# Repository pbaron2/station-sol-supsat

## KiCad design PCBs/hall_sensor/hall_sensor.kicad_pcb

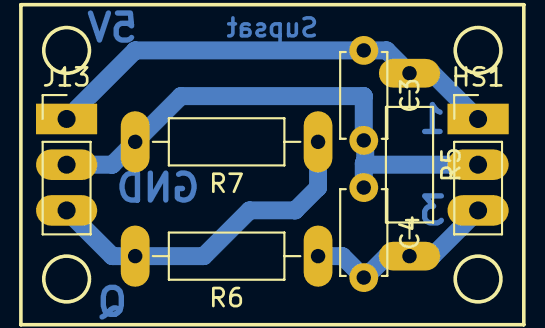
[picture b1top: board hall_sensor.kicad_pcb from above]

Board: 2 copper layers, 7 parts (0 on the bottom side), 4 nets.

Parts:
C3, C4: C; C_Disc_D4.7mm_W2.5mm_P5.00mm
HS1: HALL_SENSOR; Pin_Header_Straight_1x03_Pitch2.54mm
J13: Conn_01x03; Pin_Header_Straight_1x03_Pitch2.54mm
R5, R6, R7: R; R_Axial_DIN0207_L6.3mm_D2.5mm_P10.16mm_Horizontal

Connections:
+5V: C3.1, HS1.1, J13.1, R5.1
GNDPWR: C3.2, C4.1, HS1.2, J13.2, R7.2
unnamed: C4.2, HS1.3, R5.2, R6.1
unnamed: J13.3, R6.2, R7.1

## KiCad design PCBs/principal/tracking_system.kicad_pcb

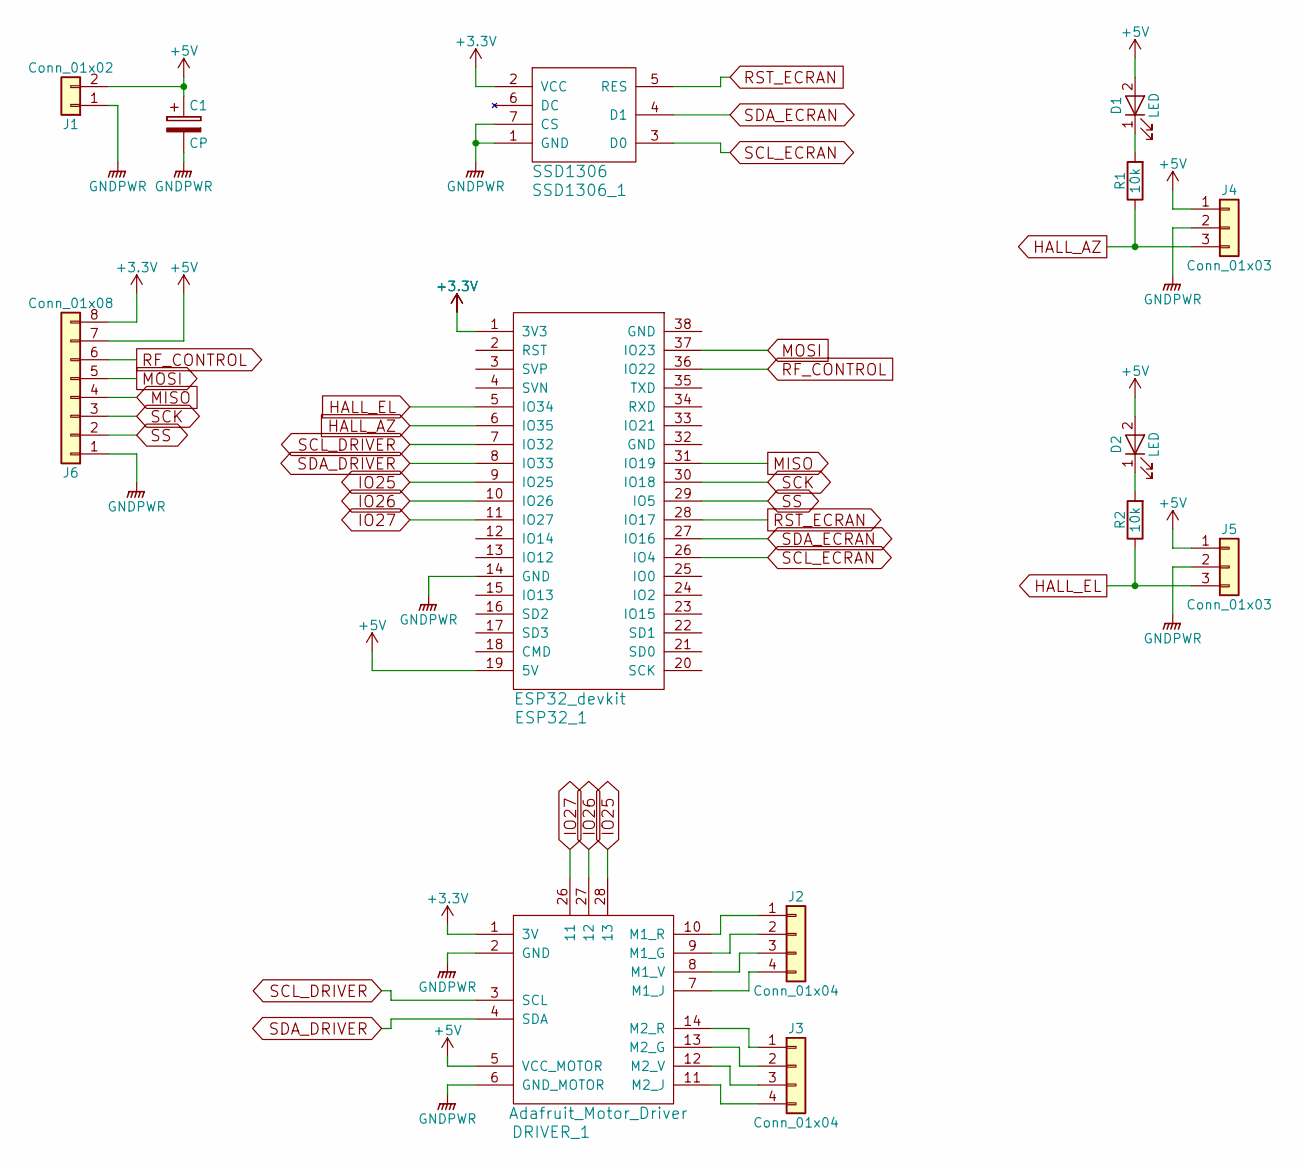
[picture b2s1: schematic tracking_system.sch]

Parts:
C1: CP; CP_Radial_D8.0mm_P2.50mm
D1, D2: LED; LED_D3.0mm
DRIVER_1: Adafruit_Motor_Driver
ESP32_1: ESP32_devkit
J1: Conn_01x02; Pin_Header_Straight_1x02_Pitch2.54mm
J2, J3: Conn_01x04; Pin_Header_Straight_1x04_Pitch2.54mm
J4, J5: Conn_01x03; Pin_Header_Straight_1x03_Pitch2.54mm
J6: Conn_01x08; Pin_Header_Straight_1x08_Pitch2.54mm
R1, R2: 10k; R_Axial_DIN0207_L6.3mm_D2.5mm_P10.16mm_Horizontal
SSD1306_1: SSD1306

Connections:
+3V3: DRIVER_1.1 (3V), ESP32_1.1 (3V3), J6.8, SSD1306_1.2 (VCC)
+5V: C1.1, D1.2 (A), D2.2 (A), DRIVER_1.5 (VCC_MOTOR), ESP32_1.19 (5V), J1.2, J4.1, J5.1, J6.7
GNDPWR: C1.2, DRIVER_1.2 (GND), DRIVER_1.6 (GND_MOTOR), ESP32_1.14 (GND), J1.1, J4.2, J5.2, J6.1, SSD1306_1.1 (GND), SSD1306_1.7 (CS)
HALL_AZ: ESP32_1.6 (IO35), J4.3, R1.1
HALL_EL: ESP32_1.5 (IO34), J5.3, R2.1
IO25: DRIVER_1.28 (13), ESP32_1.9 (IO25)
IO26: DRIVER_1.27 (12), ESP32_1.10 (IO26)
IO27: DRIVER_1.26 (11), ESP32_1.11 (IO27)
MISO: ESP32_1.31 (IO19), J6.4
MOSI: ESP32_1.37 (IO23), J6.5
unnamed: D1.1 (K), R1.2
unnamed: D2.1 (K), R2.2
unnamed: DRIVER_1.7 (M1_J), J2.4
unnamed: DRIVER_1.8 (M1_V), J2.3
unnamed: DRIVER_1.9 (M1_G), J2.2
unnamed: DRIVER_1.10 (M1_R), J2.1
unnamed: DRIVER_1.11 (M2_J), J3.4
unnamed: DRIVER_1.12 (M2_V), J3.3
unnamed: DRIVER_1.13 (M2_G), J3.2
unnamed: DRIVER_1.14 (M2_R), J3.1
RF_CONTROL: ESP32_1.36 (IO22), J6.6
RST_ECRAN: ESP32_1.28 (IO17), SSD1306_1.5 (RES)
SCK: ESP32_1.30 (IO18), J6.3
SCL_DRIVER: DRIVER_1.3 (SCL), ESP32_1.7 (IO32)
SCL_ECRAN: ESP32_1.26 (IO4), SSD1306_1.3 (D0)
SDA_DRIVER: DRIVER_1.4 (SDA), ESP32_1.8 (IO33)
SDA_ECRAN: ESP32_1.27 (IO16), SSD1306_1.4 (D1)
SS: ESP32_1.29 (IO5), J6.2

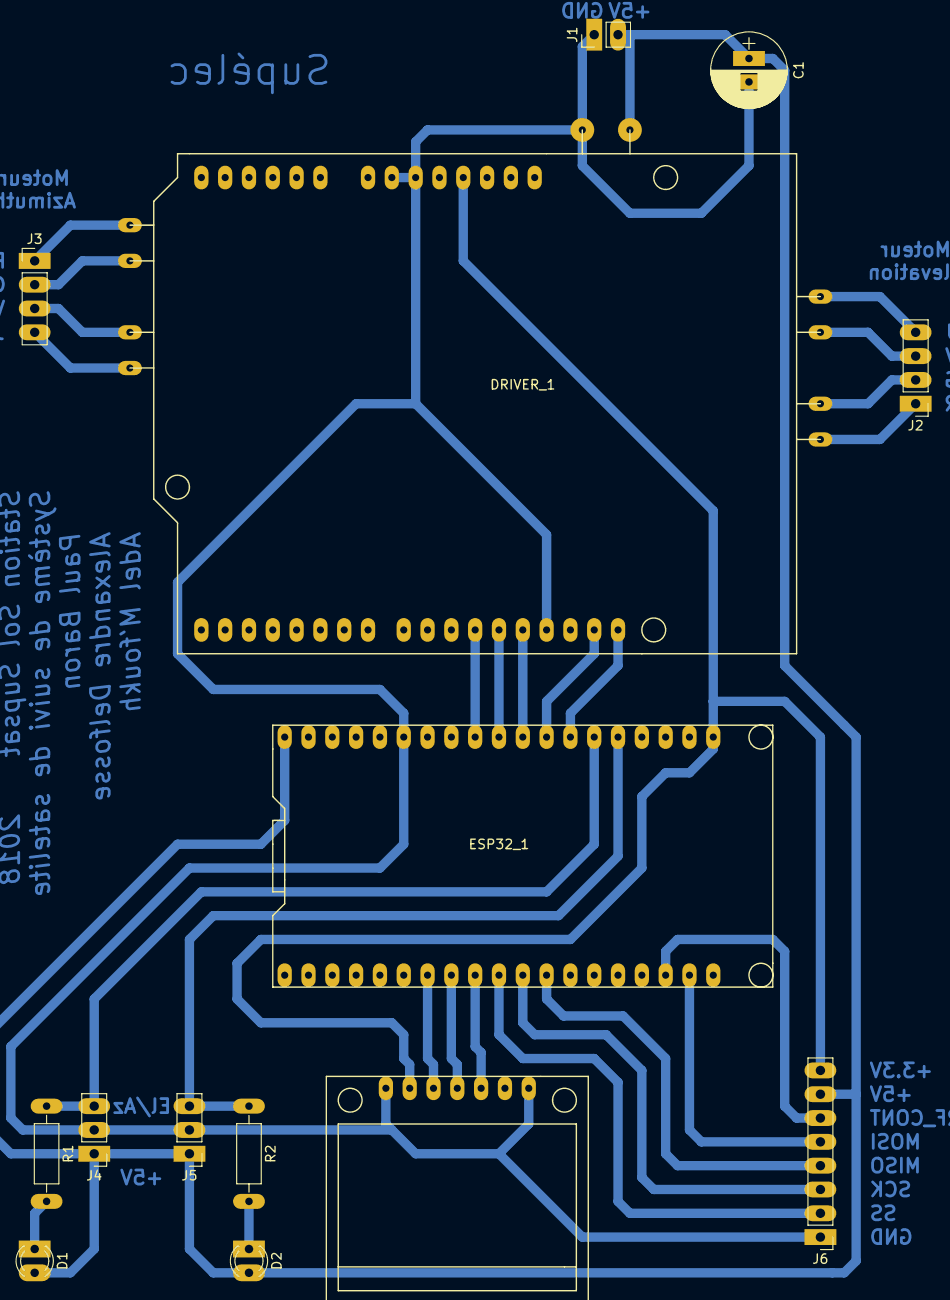
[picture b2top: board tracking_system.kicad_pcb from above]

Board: 2 copper layers, 14 parts (0 on the bottom side), 28 nets.

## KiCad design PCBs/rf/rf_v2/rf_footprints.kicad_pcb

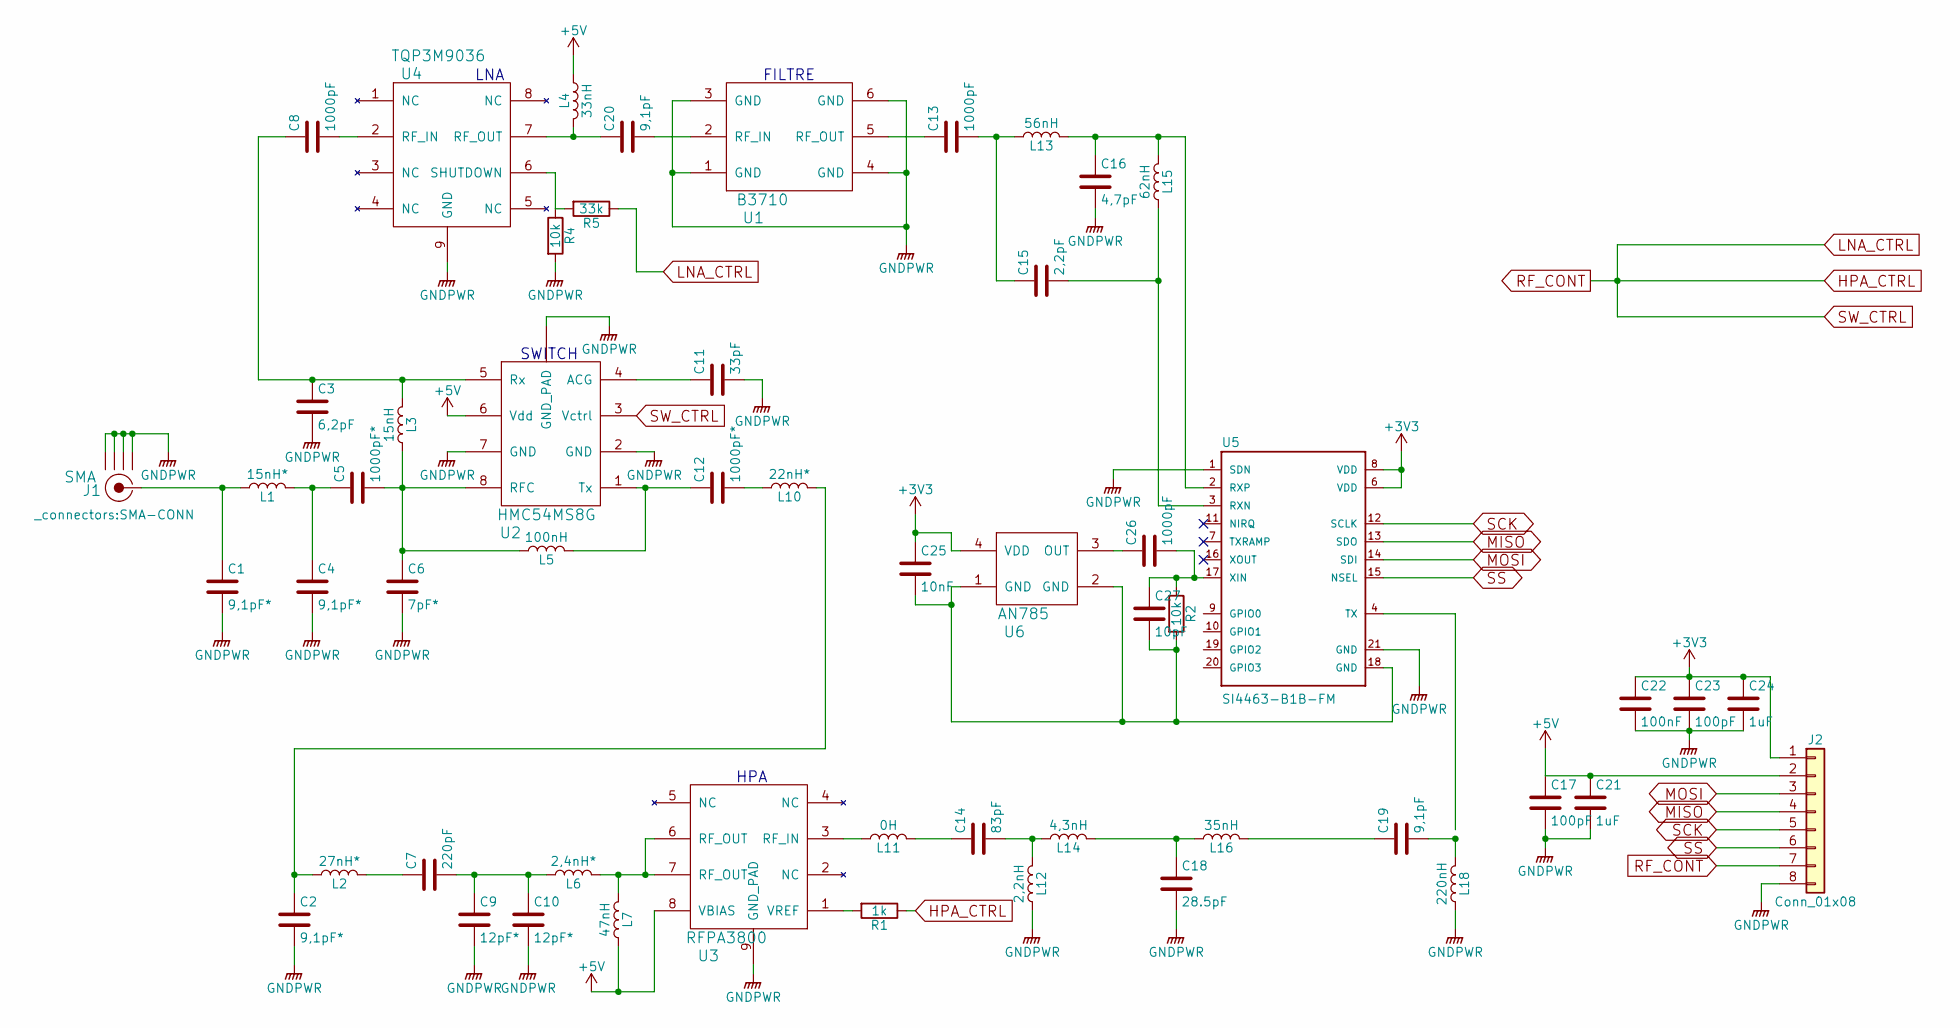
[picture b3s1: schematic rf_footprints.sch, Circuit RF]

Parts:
C1, C2, C4: 9,1pF*; C_0402_NoSilk
C3: 6,2pF; C_0402_NoSilk
C5, C12: 1000pF*; C_0402_NoSilk
C6: 7pF*; C_0402_NoSilk
C7: 220pF; C_0402_NoSilk
C8, C13, C26: 1000pF; C_0402_NoSilk
C9, C10: 12pF*; C_0402_NoSilk
C11: 33pF; C_0402_NoSilk
C14: 83pF; C_0402_NoSilk
C15: 2,2pF; C_0402_NoSilk
C16: 4,7pF; C_0402_NoSilk
C17, C23: 100pF; C_0402_NoSilk
C18: 28.5pF; C_0402_NoSilk
C19, C20: 9,1pF; C_0402_NoSilk
C21: 1uF; C_0805_HandSoldering
C22: 100nF; C_0805_HandSoldering
C24: 1uF; C_0402_NoSilk
C25: 10nF; C_0402_NoSilk
C27: 10pF; C_0402_NoSilk
J1: SMA; SMA-CONN
J2: Conn_01x08; Pin_Header_Straight_1x08_Pitch2.54mm
L1: 15nH*; L_0402
L2: 27nH*; L_0402
L3: 15nH; L_0402
L4: 33nH; L_1206_HandSoldering
L5: 100nH; L_0402
L6: 2,4nH*; L_0402
L7: 47nH; L_0603_HandSoldering
L10: 22nH*; L_0402
L11: 0H; L_0603_HandSoldering
L12: 2,2nH; L_0402
L13: 56nH; L_0402
L14: 4,3nH; L_0402
L15: 62nH; L_0402
L16: 35nH; L_0402
L18: 220nH; L_0402
R1: 1k; R_0603_HandSoldering
R2, R4: 10k; R_0402_NoSilk
R5: 33k; R_0402_NoSilk
U1: B3710; DCC6C
U2: HMC54MS8G; MSOP-8_3x3mm_Pitch0.65mm
U3: RFPA3800; SOIC-8_3.9x4.9mm_Pitch1.27mm
U4: TQP3M9036; DFN-8-1EP_2x2mm_Pitch0.5mm
U5: SI4463-B1B-FM; QFN50P400X400X90-20N
U6: AN785; Oscillator_SMD_TXC_7C-4pin_5.0x3.2mm_HandSoldering

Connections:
+3V3: C22.1, C23.1, C24.1, C25.1, J2.1, U5.6 (VDD), U5.8 (VDD), U6.4 (VDD)
+5V: C17.1, C21.1, J2.2, L4.1, L7.1, U2.6 (Vdd), U3.8 (VBIAS)
GNDPWR: C1.2, C2.2, C3.2, C4.2, C6.2, C9.2, C10.2, C11.2, C16.2, C17.2, C18.2, C21.2, C22.2, C23.2, C24.2, J1.2 (GND1), J1.3 (GND2), J1.4 (GND3), J1.5 (GND4), J2.8, L12.1, L18.1, R4.2, U1.1 (GND), U1.3 (GND), U1.4 (GND), U1.6 (GND), U2.2 (GND), U2.7 (GND), U2.~ (GND_PAD), U3.9 (GND_PAD), U4.9 (GND), U5.1 (SDN), U5.21 (GND)
HPA_CTRL: J2.7, R1.1, R5.1, U2.3 (Vctrl)
MISO: J2.4, U5.13 (SDO)
MOSI: J2.3, U5.14 (SDI)
unnamed: C1.1, J1.1 (RF), L1.1
unnamed: C2.1, L2.1, L10.2
unnamed: C3.1, C8.1, L3.2, U2.5 (Rx)
unnamed: C4.1, C5.1, L1.2
unnamed: C5.2, C6.1, L3.1, L5.1, U2.8 (RFC)
unnamed: C7.1, L2.2
unnamed: C8.2, U4.2 (RF_IN)
unnamed: C7.2, C9.1, C10.1, L6.1
unnamed: C11.1, U2.4 (ACG)
unnamed: C12.1, L5.2, U2.1 (Tx)
unnamed: C12.2, L10.1
unnamed: C13.1, U1.5 (RF_OUT)
unnamed: C13.2, C15.1, L13.1
unnamed: C14.1, L11.2
unnamed: C14.2, L12.2, L14.1
unnamed: C15.2, L15.1, U5.3 (RXN)
unnamed: C16.1, L13.2, L15.2, U5.2 (RXP)
unnamed: C18.1, L14.2, L16.1
unnamed: C19.1, L16.2
unnamed: C19.2, L18.2
unnamed: C20.1, L4.2, U4.7 (RF_OUT)
unnamed: C20.2, U1.2 (RF_IN)
unnamed: C25.2, C27.2, R2.2, U5.18 (GND), U6.1 (GND), U6.2 (GND)
unnamed: C26.1, U6.3 (OUT)
unnamed: C26.2, C27.1, R2.1, U5.17 (XIN)
unnamed: L6.2, L7.2, U3.6 (RF_OUT), U3.7 (RF_OUT)
unnamed: L11.1, U3.3 (RF_IN)
unnamed: R1.2, U3.1 (VREF)
unnamed: R4.1, R5.2, U4.6 (SHUTDOWN)
SCK: J2.5, U5.12 (SCLK)
SS: J2.6, U5.15 (NSEL)

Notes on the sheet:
SWITCH
LNA
FILTRE
HPA

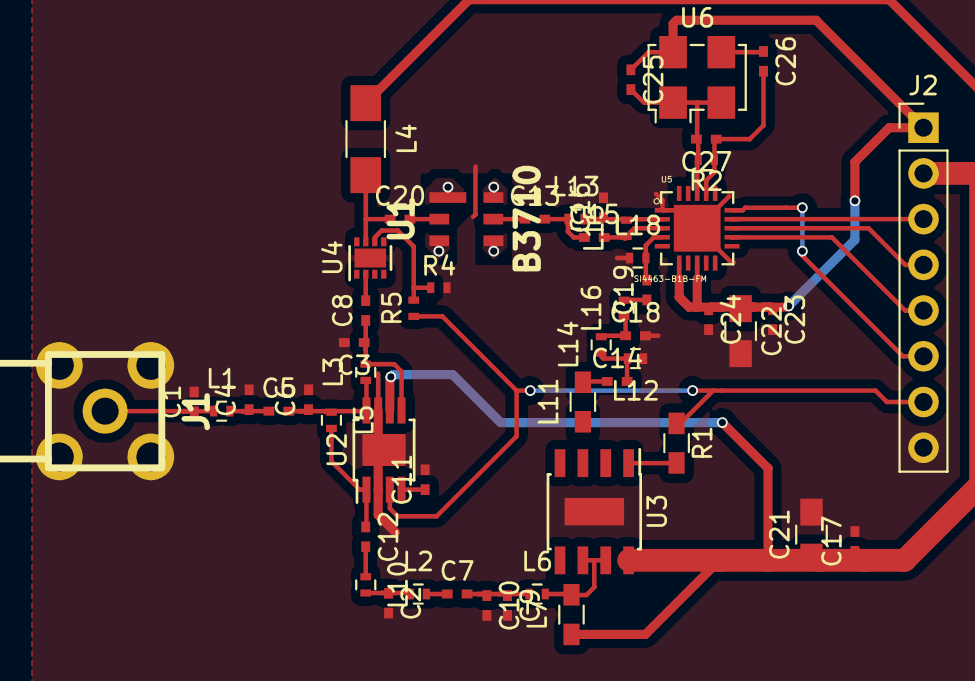
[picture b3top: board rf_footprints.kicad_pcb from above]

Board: 2 copper layers, 54 parts (0 on the bottom side), 37 nets.
